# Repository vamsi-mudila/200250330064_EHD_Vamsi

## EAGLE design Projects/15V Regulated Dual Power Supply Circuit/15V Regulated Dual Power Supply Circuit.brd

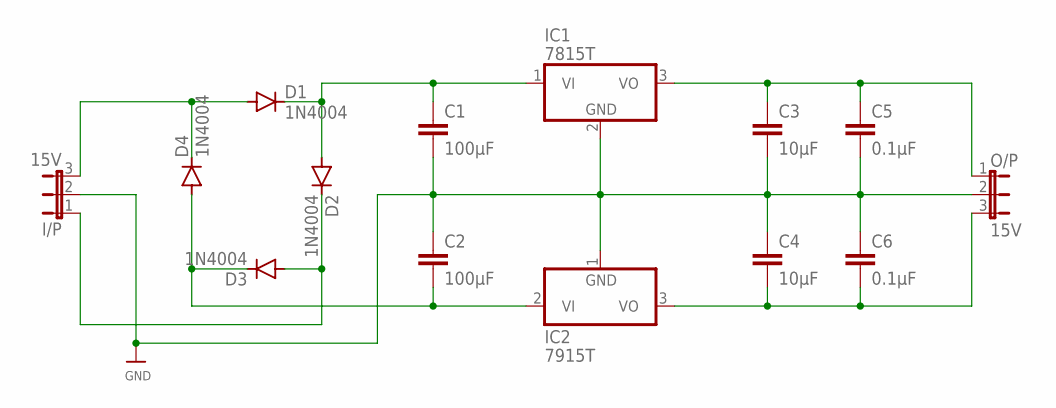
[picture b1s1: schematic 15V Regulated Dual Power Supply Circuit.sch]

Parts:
C1, C2: 100μF; C2.5-2
C3, C4: 10μF; C2.5-2
C5, C6: 0.1μF; C2.5-2
D1, D2, D3, D4: 1N4004; DO41-10
I/P: 15V; JP2
IC1: 7815T; TO220H
IC2: 7915T; TO220H
O/P: 15V; JP2

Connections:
GND: C1.2, C2.1, C3.2, C4.1, C5.2, C6.1, I/P.2, IC1.2 (GND), IC2.1 (GND), O/P.2
unnamed: D1.A, D4.C, I/P.3
unnamed: C1.1, D1.C, D2.A, IC1.1 (VI)
unnamed: D2.C, D3.A, I/P.1
unnamed: C2.2, D3.C, D4.A, IC2.2 (VI)
unnamed: C4.2, C6.2, IC2.3 (VO), O/P.3
unnamed: C3.1, C5.1, IC1.3 (VO), O/P.1

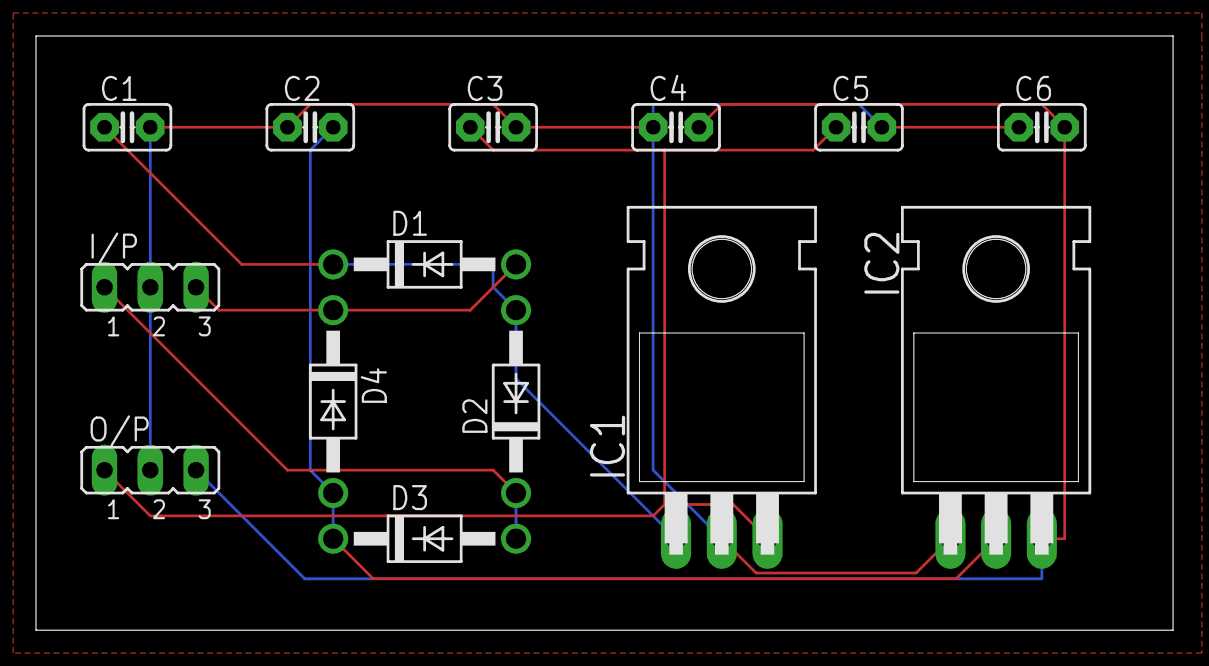
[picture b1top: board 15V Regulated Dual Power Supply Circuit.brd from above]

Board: 2 copper layers, 63.2 x 33.0 mm, 14 parts (0 on the bottom side), 7 nets.

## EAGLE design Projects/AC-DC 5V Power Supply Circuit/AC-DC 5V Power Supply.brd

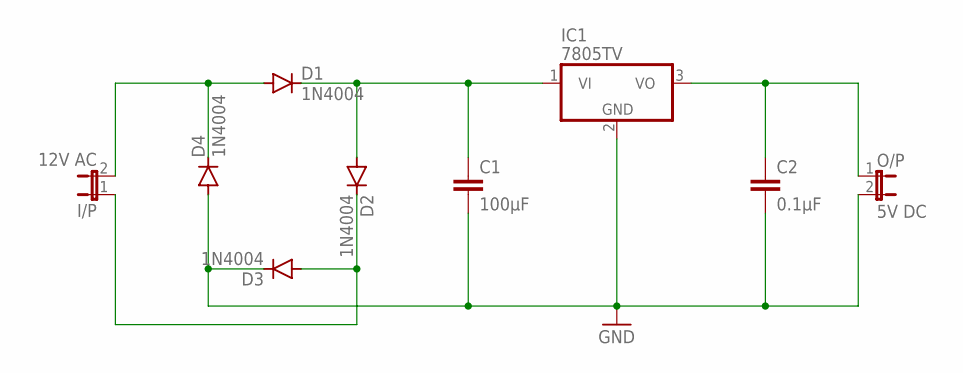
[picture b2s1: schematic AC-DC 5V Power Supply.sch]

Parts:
C1: 100μF; C2.5-2
C2: 0.1μF; C2.5-2
D1, D2, D3, D4: 1N4004; DO41-10
I/P: 12V AC; JP1
IC1: 7805TV; TO220V
O/P: 5V DC; JP1

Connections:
GND: C1.2, C2.2, D3.C, D4.A, IC1.2 (GND), O/P.2
unnamed: D1.A, D4.C, I/P.2
unnamed: C1.1, D1.C, D2.A, IC1.1 (VI)
unnamed: D2.C, D3.A, I/P.1
unnamed: C2.1, IC1.3 (VO), O/P.1

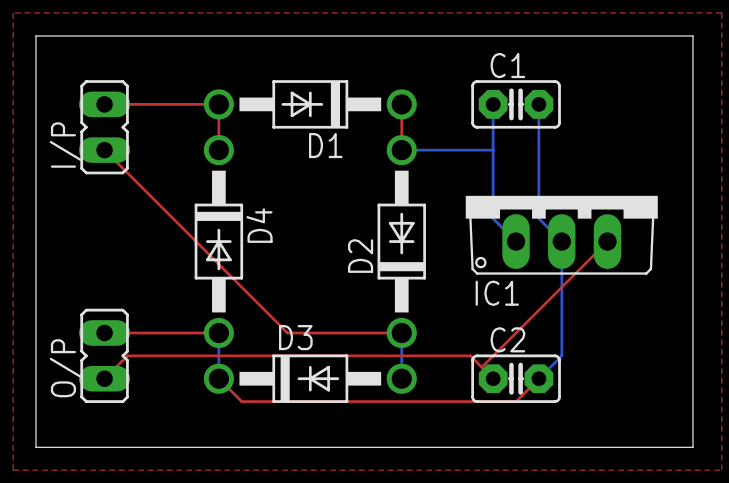
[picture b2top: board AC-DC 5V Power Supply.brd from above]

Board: 2 copper layers, 36.5 x 22.9 mm, 9 parts (0 on the bottom side), 5 nets.

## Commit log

2020-10-02 Create .AC-DC 5V
2020-10-02 Create .15V Regulated Dual
